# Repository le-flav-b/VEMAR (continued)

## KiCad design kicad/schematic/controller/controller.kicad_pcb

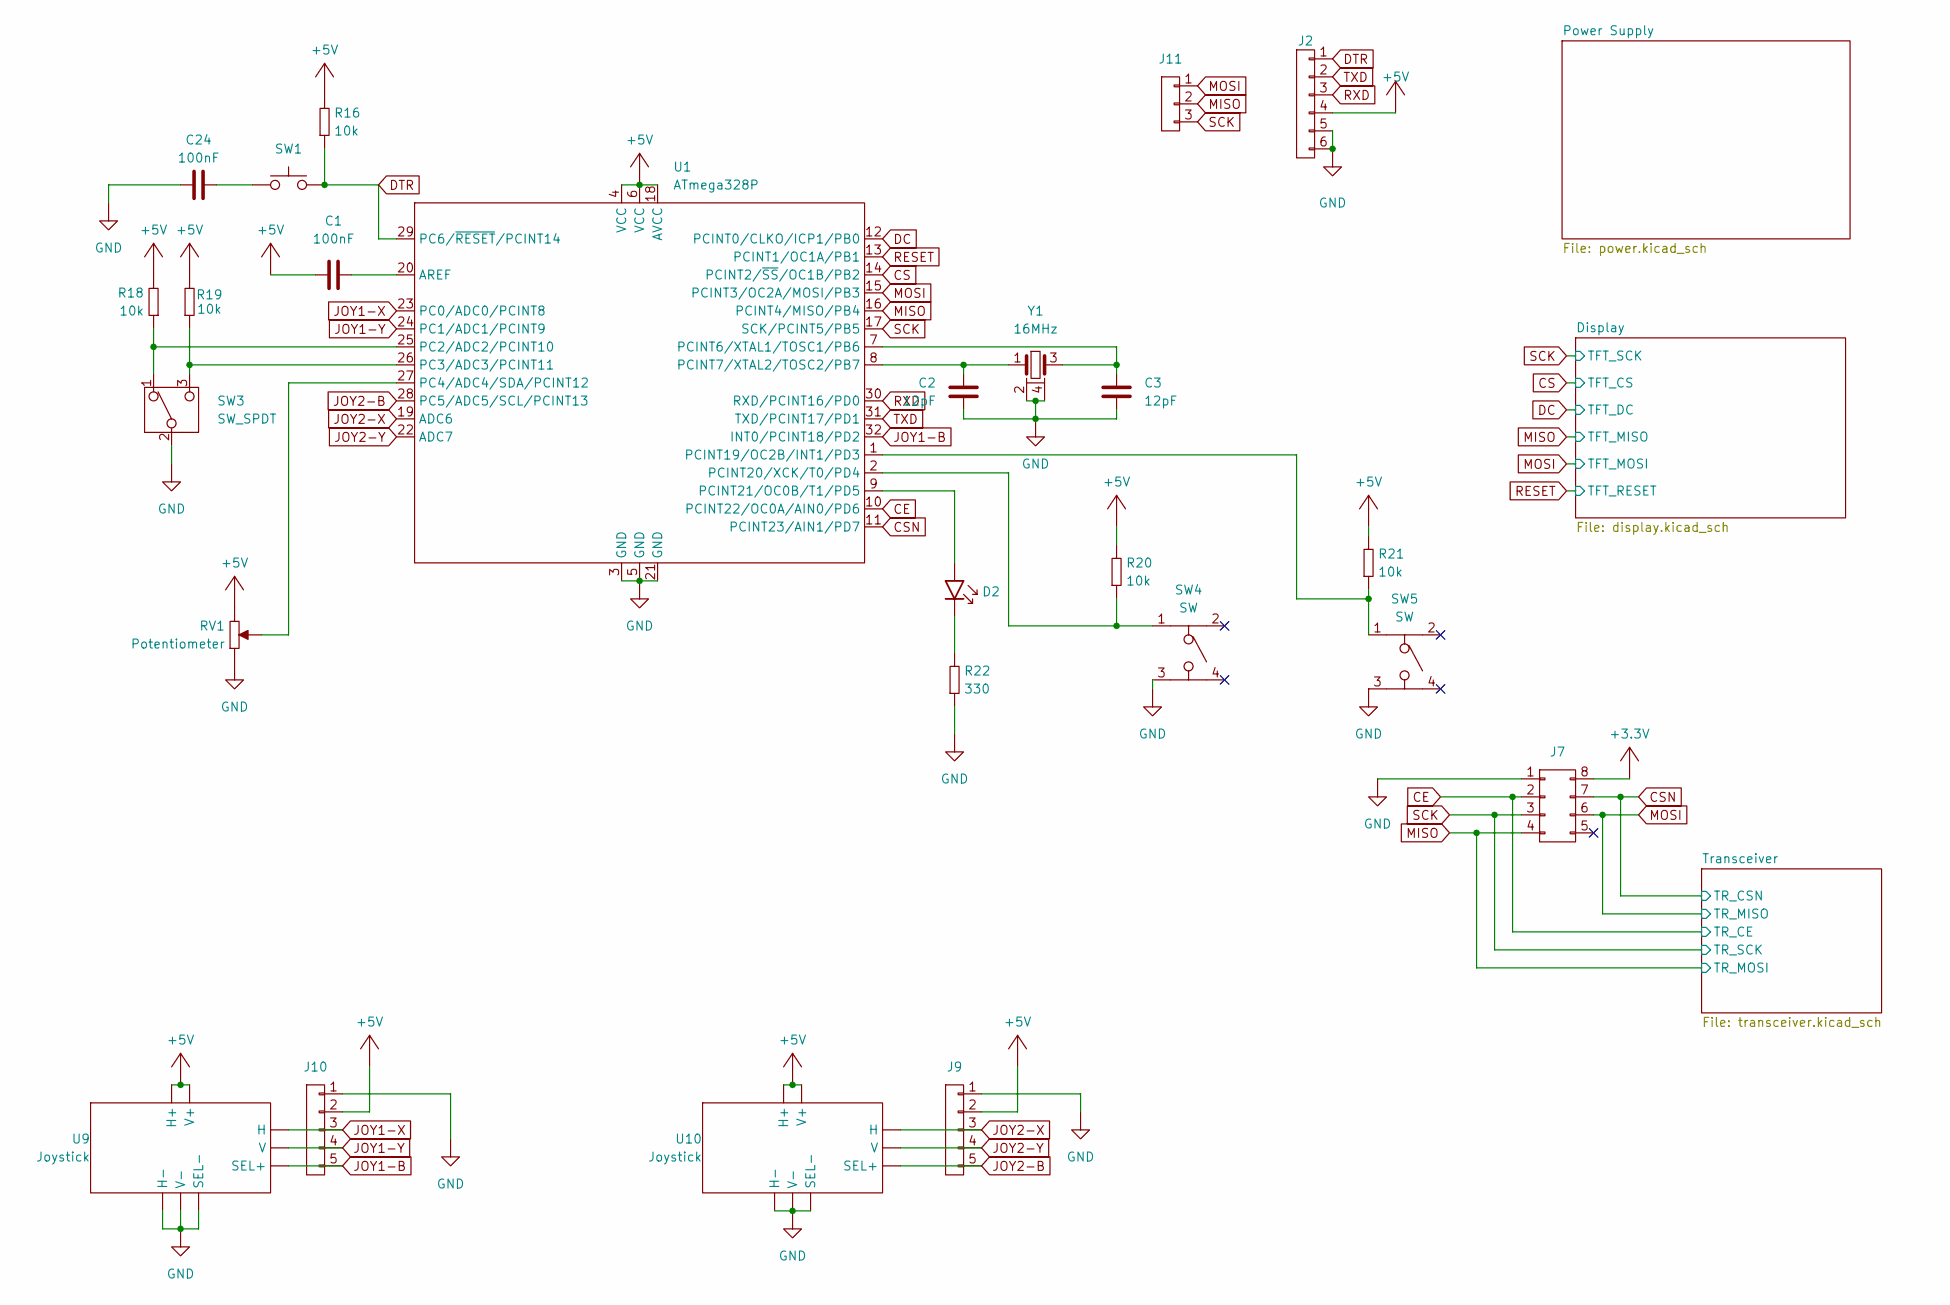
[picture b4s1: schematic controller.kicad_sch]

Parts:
C1, C24: 100nF; C_0603; Manufacturer Part CC0603KRX7R9BB104; LCSC Part C14663
C2, C3: 12pF; C_0603; Manufacturer Part CC0603JRNPO9BN120; LCSC Part C107034
D2: Green; LED_0603; Manufacturer Part YLED0603G; LCSC Part C19273151
J2: 01x06; Pin_01x06
J7: 02x04; Pin_02x04
J9, J10: 01x05; Pin_01x05
J11: 01x03; Pin_01x03
R16, R18, R19, R20, R21: 10k; R_0603; Manufacturer Part FRC0603F1002TS; LCSC Part C2906982
R22: 330; R_0603; Manufacturer Part FRC0603J331 TS; LCSC Part C2907152
RV1: Potentiometer; RV_45; Manufacturer Part PTA4543-2015DPB103; LCSC Part C17444183
SW1: Reset; SW_Tactile3x2.5; Manufacturer Part HX-B3U-1000P-1.6N; LCSC Part C49234121
SW3: SW_SPDT; SW_Toggle; Manufacturer Part MST103; LCSC Part AliExpress
SW4, SW5: SW; SW_Tactile12x12; Manufacturer Part TS-1094TS-B3D2-T-Y; LCSC Part C19077684
U1: ATmega328P; ATmega328p_TQFP; Manufacturer Part ATMEGA328P-AU; LCSC Part C14877
U9, U10: Joystick; Manufacturer Part Hall-Effect Joysticks; LCSC Part AliExpress
Y1: 16MHz; Crystal_3225; Manufacturer Part X322516MLB4SI; LCSC Part C13738

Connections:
+3.3V: J7.8; also elsewhere on the board
+5V: C1.1, J2.4, J9.2, J10.2, R16.2, R18.2, R19.2, R20.2, R21.2, RV1.3, U1.4 (VCC), U1.6 (VCC), U1.18 (AVCC), U9.H3 (H+), U9.V3 (V+), U10.H3 (H+), U10.V3 (V+); also elsewhere on the board
CE: J7.2, U1.10 (PCINT22/OC0A/AIN0/PD6); also elsewhere on the board
CS: U1.14 (PCINT2/~SS/OC1B/PB2); also elsewhere on the board
CSN: J7.7, U1.11 (PCINT23/AIN1/PD7); also elsewhere on the board
DC: U1.12 (PCINT0/CLKO/ICP1/PB0); also elsewhere on the board
DTR: J2.1, R16.1, SW1.2, U1.29 (PC6/~RESET/PCINT14)
JOY1-B: J10.5, U1.32 (INT0/PCINT18/PD2), U9.B2A (SEL+), U9.B2B; also elsewhere on the board
JOY1-X: J10.3, U1.23 (PC0/ADC0/PCINT8), U9.H2 (H)
JOY1-Y: J10.4, U1.24 (PC1/ADC1/PCINT9), U9.V2 (V)
JOY2-B: J9.5, U1.28 (PC5/ADC5/SCL/PCINT13), U10.B2A (SEL+), U10.B2B; also elsewhere on the board
JOY2-X: J9.3, U1.19 (ADC6), U10.H2 (H)
JOY2-Y: J9.4, U1.22 (ADC7), U10.V2 (V)
MISO: J7.4, J11.2, U1.16 (PCINT4/MISO/PB4); also elsewhere on the board
MOSI: J7.6, J11.1, U1.15 (PCINT3/OC2A/MOSI/PB3); also elsewhere on the board
unnamed: C24.2, SW1.1
unnamed: D2.2 (A), U1.9 (PCINT21/OC0B/T1/PD5)
unnamed: D2.1 (K), R22.2
unnamed: C1.2, U1.20 (AREF)
unnamed: R18.1, SW3.1, U1.25 (PC2/ADC2/PCINT10)
unnamed: R19.1, SW3.3, U1.26 (PC3/ADC3/PCINT11)
unnamed: RV1.2, U1.27 (PC4/ADC4/SDA/PCINT12)
unnamed: C3.2, U1.7 (PCINT6/XTAL1/TOSC1/PB6), Y1.3
unnamed: C2.2, U1.8 (PCINT7/XTAL2/TOSC2/PB7), Y1.1
unnamed: R21.1, SW5.1, U1.1 (PCINT19/OC2B/INT1/PD3)
unnamed: R20.1, SW4.1, U1.2 (PCINT20/XCK/T0/PD4)
RESET: U1.13 (PCINT1/OC1A/PB1); also elsewhere on the board
RXD: J2.3, U1.30 (RXD/PCINT16/PD0)
SCK: J7.3, J11.3, U1.17 (SCK/PCINT5/PB5); also elsewhere on the board
TXD: J2.2, U1.31 (TXD/PCINT17/PD1)

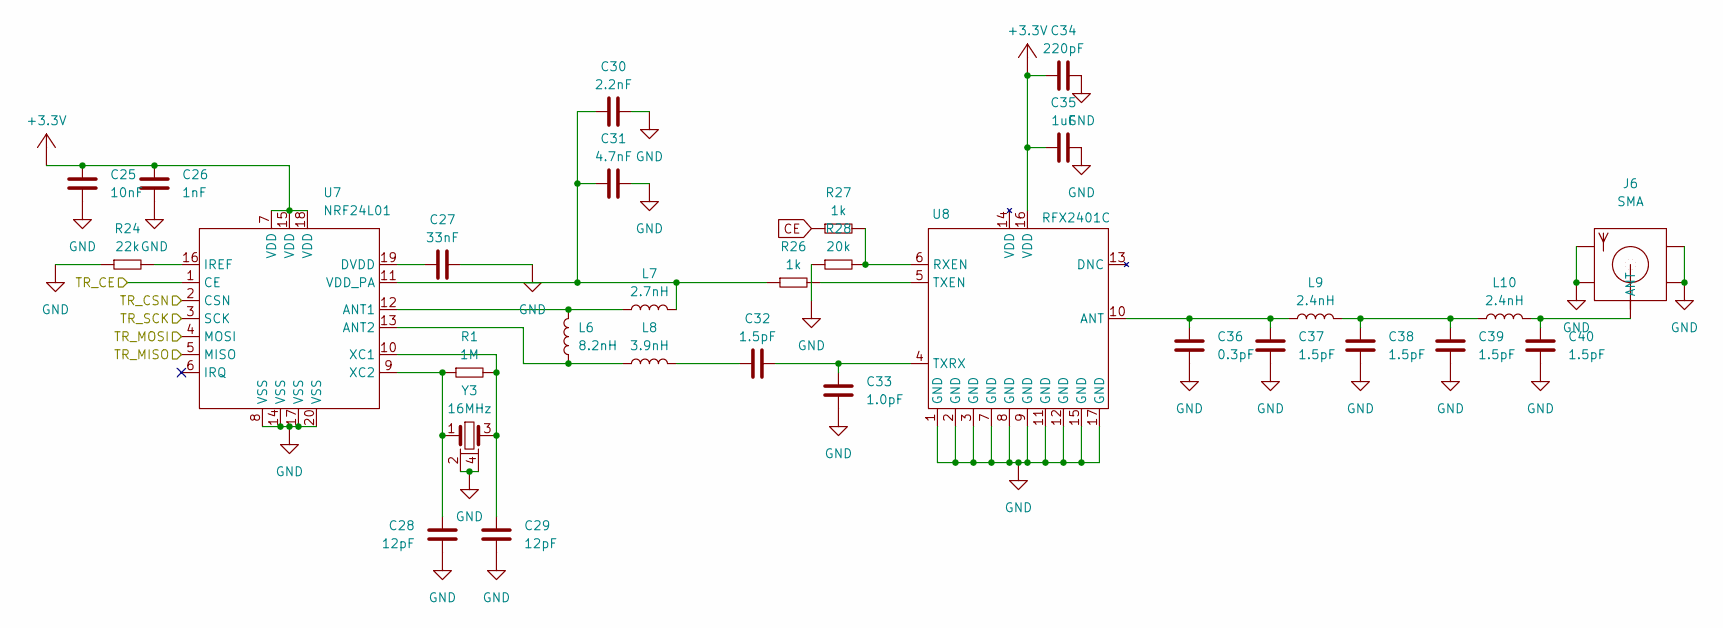
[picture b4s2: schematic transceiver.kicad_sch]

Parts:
C25: 10nF; C_0603; Manufacturer Part CL10B103KB8NNNC; LCSC Part C1589
C26: 1nF; C_0603; Manufacturer Part CL10B102KB8NNNC; LCSC Part C1588
C27: 33nF; C_0603; Manufacturer Part C0603C333K4RAC7867; LCSC Part C599735
C28, C29: 12pF; C_0603; Manufacturer Part CC0603JRNPO9BN120; LCSC Part C107034
C30: 2.2nF; C_0603; Manufacturer Part CL10C222JB8NNNC; LCSC Part C33353
C31: 4.7nF; C_0603; Manufacturer Part CL10B472KB8NNNC; LCSC Part C1621
C32, C37, C38, C39, C40: 1.5pF; C_0603; Manufacturer Part TCC0603COG1R5C500CT; LCSC Part C376772
C33: 1.0pF; C_0603; Manufacturer Part FCC0603N1R0C500CT; LCSC Part C5137611
C34: 220pF; C_0603; Manufacturer Part CC0603KRX7R9BB221; LCSC Part C107081
C35: 1uF; C_0603; Manufacturer Part CL10A105KP8NNNC; LCSC Part C26413
C36: 0.3pF; C_0603; Manufacturer Part TCC0603COG0R3B500CT; LCSC Part C5375816
J6: SMA; Manufacturer Part SMA PCB; LCSC Part AliExpress
L6: 8.2nH; L_0603; Manufacturer Part SCC1608C8N2JSP; LCSC Part C412032
L7: 2.7nH; L_0603; Manufacturer Part BSCH001608082N7S00; LCSC Part C5252358
L8: 3.9nH; L_0603; Manufacturer Part HBLS1608-3N9S; LCSC Part C964023
L9, L10: 2.4nH; L_0603; Manufacturer Part VHF160808H2N4ST; LCSC Part C395082
R1: 1M; R_0603; Manufacturer Part PA0603FRP070R001L; LCSC Part C6949223
R24: 22k; R_0603; Manufacturer Part FRC0603J223 TS; LCSC Part C2907128
R26, R27: 1k; R_0603; Manufacturer Part FRC0603J102 TS; LCSC Part C2907113
R28: 20k; R_0603; Manufacturer Part FRC0603J203 TS; LCSC Part C2907124
U7: NRF24L01; NRF24L01_QFN20; Manufacturer Part NRF24L01P-R; LCSC Part C8791
U8: RFX2401C; RFX2401C_QFN16; Manufacturer Part RFX2401C; LCSC Part C19213
Y3: 16MHz; Crystal_3225; Manufacturer Part X322516MLB4SI; LCSC Part C13738

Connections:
+3.3V: C25.2, C26.2, C34.1, C35.1, U7.7 (VDD), U7.15 (VDD), U7.18 (VDD), U8.16 (VDD); also elsewhere on the board
CE: R27.1, U7.1 (CE); also elsewhere on the board
CSN: U7.2 (CSN); also elsewhere on the board
MISO: U7.4 (MOSI); also elsewhere on the board
MOSI: U7.5 (MISO); also elsewhere on the board
unnamed: C32.1, L8.2
unnamed: C38.2, C39.2, L9.2, L10.1
unnamed: C40.2, J6.1 (ANT), L10.2
unnamed: L6.2, L7.1, U7.12 (ANT1)
unnamed: L6.1, L8.1, U7.13 (ANT2)
unnamed: C27.1, U7.19 (DVDD)
unnamed: R24.2, U7.16 (IREF)
unnamed: C30.1, C31.1, L7.2, R26.1, U7.11 (VDD_PA)
unnamed: C29.2, R1.2, U7.10 (XC1), Y3.3
unnamed: C28.2, R1.1, U7.9 (XC2), Y3.1
unnamed: C36.2, C37.2, L9.1, U8.10 (ANT)
unnamed: R27.2, R28.2, U8.6 (RXEN)
unnamed: R26.2, U8.5 (TXEN)
unnamed: C32.2, C33.2, U8.4 (TXRX)
SCK: U7.3 (SCK); also elsewhere on the board

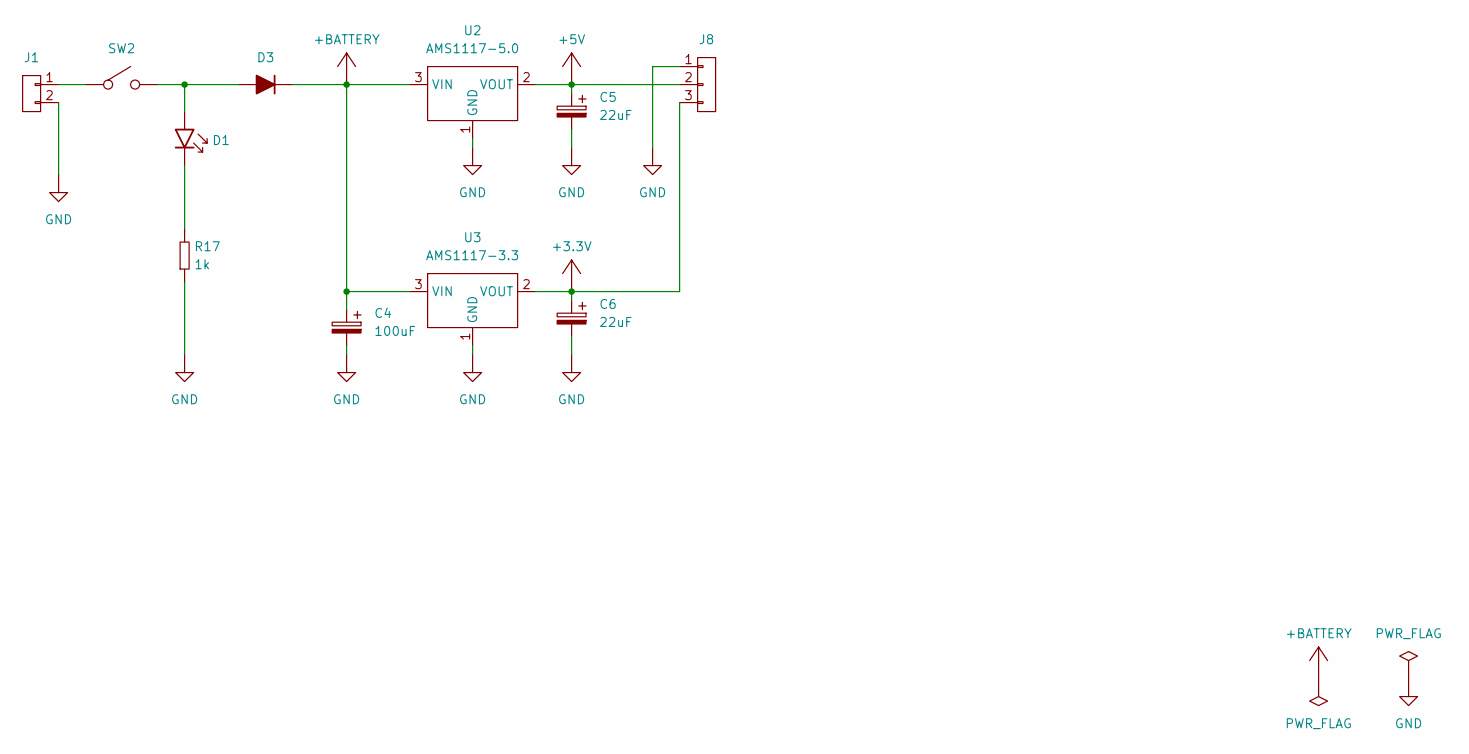
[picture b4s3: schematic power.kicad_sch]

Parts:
C4: 100uF; C_D6.3xL5.4; Manufacturer Part RVT1V101M0605; LCSC Part C3151830
C5, C6: 22uF; C_D6.3xL5.4; Manufacturer Part RVT1H220M0605; LCSC Part C72505
D1: Red; LED_0603; Manufacturer Part YLED0603R; LCSC Part C19171390
D3: Diode; D_SOD123; Manufacturer Part 1N4007; LCSC Part C2892681
J1: 01x02; Pin_01x02
J8: 01x03; Pin_01x03
R17: 1k; R_0603; Manufacturer Part FRC0603J102 TS; LCSC Part C2907113
SW2: Power; SW_Slide9.1x3.5; Manufacturer Part MST-12D18G4 SPDT Slide Switch; LCSC Part C49023767
U2: AMS1117-5.0; AMS1117-SOT223; Manufacturer Part AMS1117-3.3; LCSC Part C347222
U3: AMS1117-3.3; AMS1117-SOT223; Manufacturer Part AMS1117-5.0; LCSC Part C347223

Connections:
+3.3V: C6.1, J8.3, U3.2 (VOUT); also elsewhere on the board
+5V: C5.1, J8.2, U2.2 (VOUT); also elsewhere on the board
unnamed: D1.2 (A), D3.2 (A), SW2.2
unnamed: D1.1 (K), R17.2
unnamed: J1.1, SW2.1

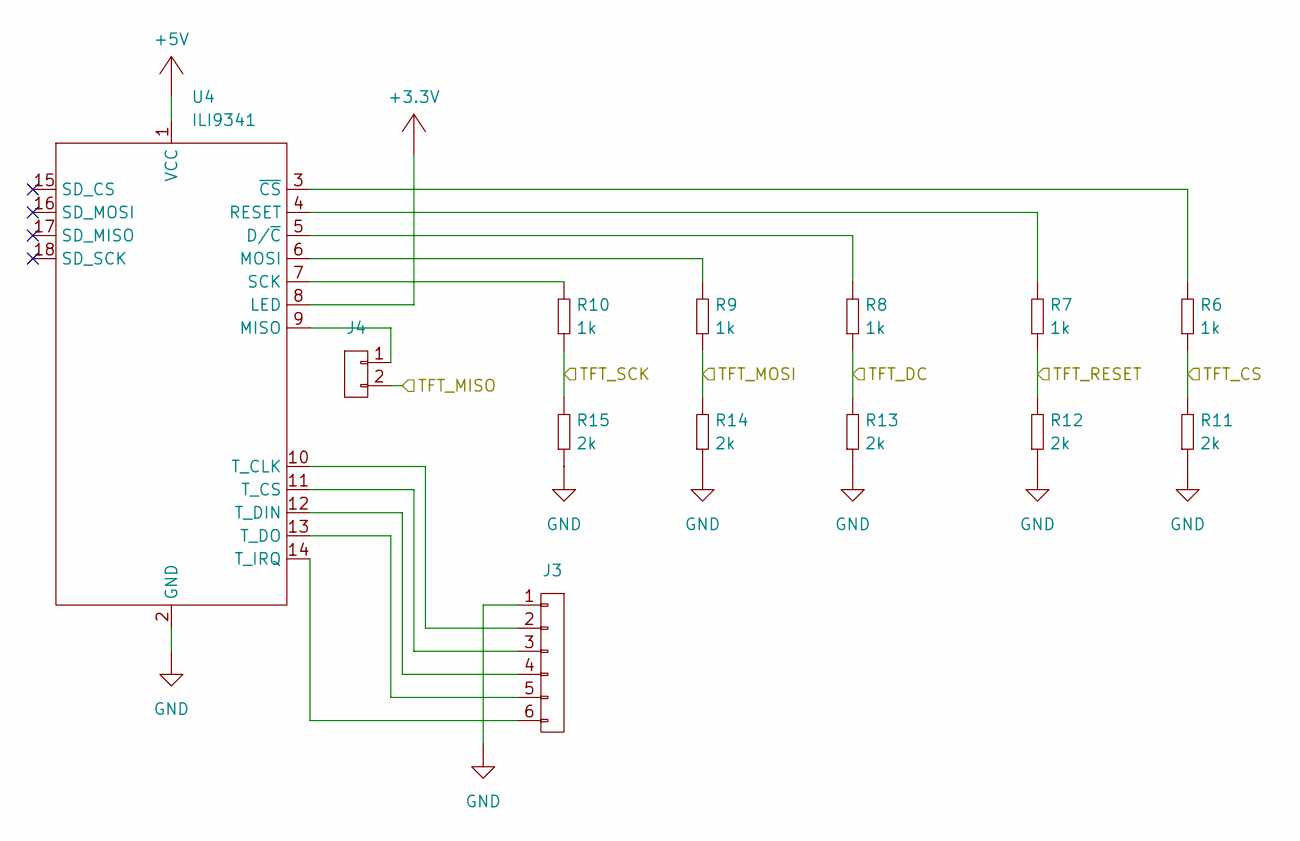
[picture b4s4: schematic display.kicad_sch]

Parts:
J3: 01x06; Pin_01x06
J4: 01x02; Pin_01x02
R6, R7, R8, R9, R10: 1k; R_0603; Manufacturer Part FRC0603J102 TS; LCSC Part C2907113
R11, R12, R13, R14, R15: 2k; R_0603; Manufacturer Part FRC0603F2001TS; LCSC Part C2907022
U4: ILI9341

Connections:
+3.3V: U4.8 (LED); also elsewhere on the board
+5V: U4.1 (VCC); also elsewhere on the board
CS: R6.1, R11.2; also elsewhere on the board
DC: R8.1, R13.2; also elsewhere on the board
MISO: J4.2; also elsewhere on the board
MOSI: R9.1, R14.2; also elsewhere on the board
unnamed: R8.2, U4.5 (D/~C)
unnamed: J4.1, U4.9 (MISO)
unnamed: R9.2, U4.6 (MOSI)
unnamed: R7.2, U4.4 (RESET)
unnamed: R10.2, U4.7 (SCK)
unnamed: J3.2, U4.10 (T_CLK)
unnamed: J3.3, U4.11 (T_CS)
unnamed: J3.4, U4.12 (T_DIN)
unnamed: J3.5, U4.13 (T_DO)
unnamed: J3.6, U4.14 (T_IRQ)
unnamed: R6.2, U4.3 (~CS)
RESET: R7.1, R12.2; also elsewhere on the board
SCK: R10.1, R15.2; also elsewhere on the board

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
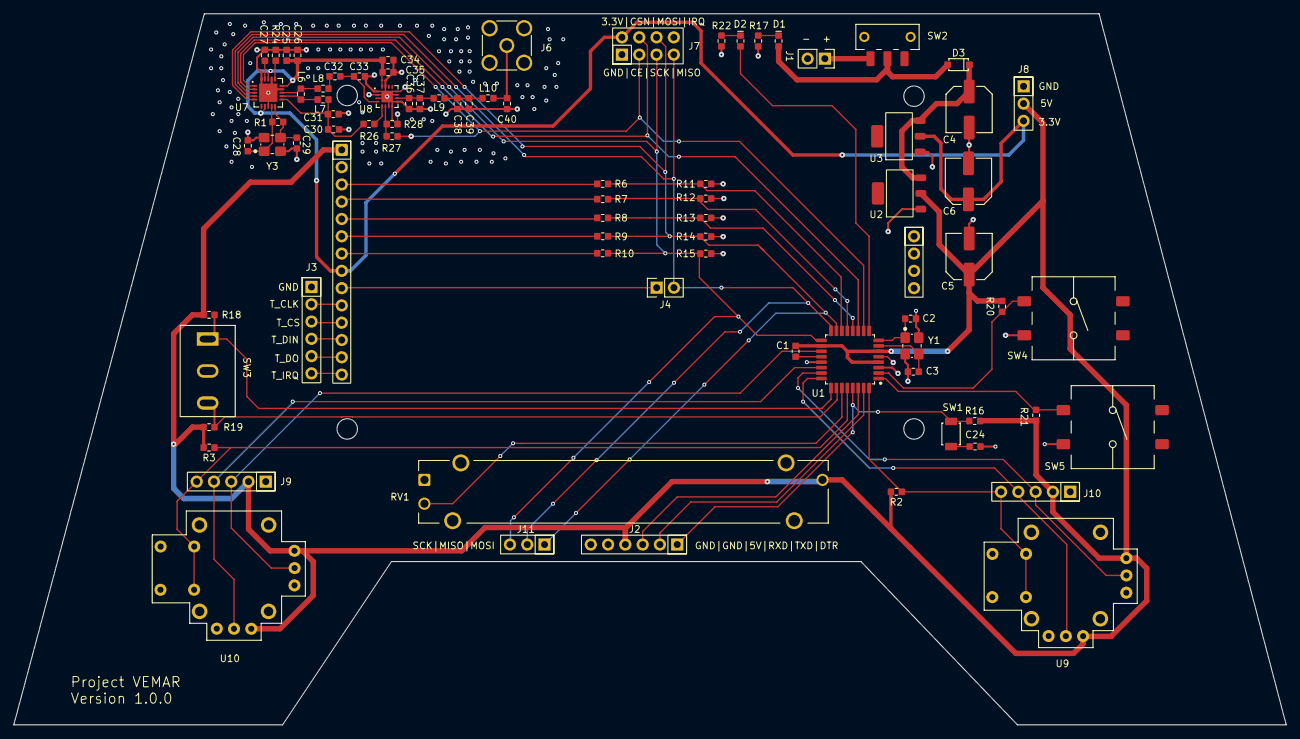
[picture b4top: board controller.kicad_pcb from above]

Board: 2 copper layers, 187.0 x 104.5 mm, 81 parts (0 on the bottom side), 60 nets.

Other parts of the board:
R2, R3: 10k; R_0603

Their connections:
+5V: R2.2, R3.2; also elsewhere on the board
JOY1-B: R2.1; also elsewhere on the board
JOY2-B: R3.1; also elsewhere on the board
